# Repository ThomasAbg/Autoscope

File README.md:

# Autoscope

Autoscope is a 3D printed Dobson telescope automated by a Raspberry-Pi 3.

## Dependent repositories

The Yocto layer to build the telecope OS :

- https://github.com/thomaslepoix/meta-autoscope

The Stellarium plugin to control the telescope :

- https://github.com/thibaudledo/Autoscope-Stellarium-plugin

<br>

## Branch & release organization

- [branch : master](https://github.com/thibaudledo/Autoscope/tree/master) : Readme & main software
- [release : alpha](https://github.com/thibaudledo/Autoscope/releases) : Out of the box packages (Stellarium, OS)
- [branch : hardware](https://github.com/thibaudledo/Autoscope/tree/hardware) : 3D blender files & PCB kicad files
- [branch : doc](https://github.com/thibaudledo/Autoscope/tree/doc) : Documentation, datasheets, etc.
- [branch : latex](https://github.com/thibaudledo/Autoscope/tree/latex) : Latex documents
- [branch : hello_mod](https://github.com/thibaudledo/Autoscope/tree/hello_mod) : Exemple, helloworld kernel module
- [branch : mpu9250_mod](https://github.com/thibaudledo/Autoscope/tree/mpu9250_mod) : IMU driver
- [branch : a4988_mod](https://github.com/thibaudledo/Autoscope/tree/a4988_mod) : Motors & position sensors driver
- [branch : mtk3339d](https://github.com/thibaudledo/Autoscope/tree/mtk3339d) : GPS driver

<br>

## Download & work on this repository

```
mkdir Autoscope/
cd Autoscope/
git clone https://github.com/thibaudledo/Autoscope -b master Master
git clone https://github.com/thibaudledo/Autoscope -b doc Documentation
git clone https://github.com/thibaudledo/Autoscope -b latex Latex
git clone https://github.com/thibaudledo/Autoscope -b hardware Hardware

git clone https://github.com/thibaudledo/Autoscope -b hello_mod hello-mod
git clone https://github.com/thibaudledo/Autoscope -b mpu9250_mod mpu9250-mod
git clone https://github.com/thibaudledo/Autoscope -b a4988_mod a4988-mod
git clone https://github.com/thibaudledo/Autoscope -b mtk3339d mtk3339d
```

<br>

## Authors

- [Thibaud Le Doledec](https://github.com/thibaudledo) `<thibaudledo@gmail.com>`
- [Thomas Lepoix](https://github.com/thomaslepoix) `<thomas.lepoix@protonmail.ch>`
- [Thomas Abgrall](https://github.com/ThomasAbg) `<01thomas.abgrall@gmail.com>`
- [Clément Ailloud](https://github.com/clement-ailloud) `<clem.ailloud@gmail.com>`

<br>

## Inspired by

- https://blog.dagoma.fr/telescope-imprime-en-3d/

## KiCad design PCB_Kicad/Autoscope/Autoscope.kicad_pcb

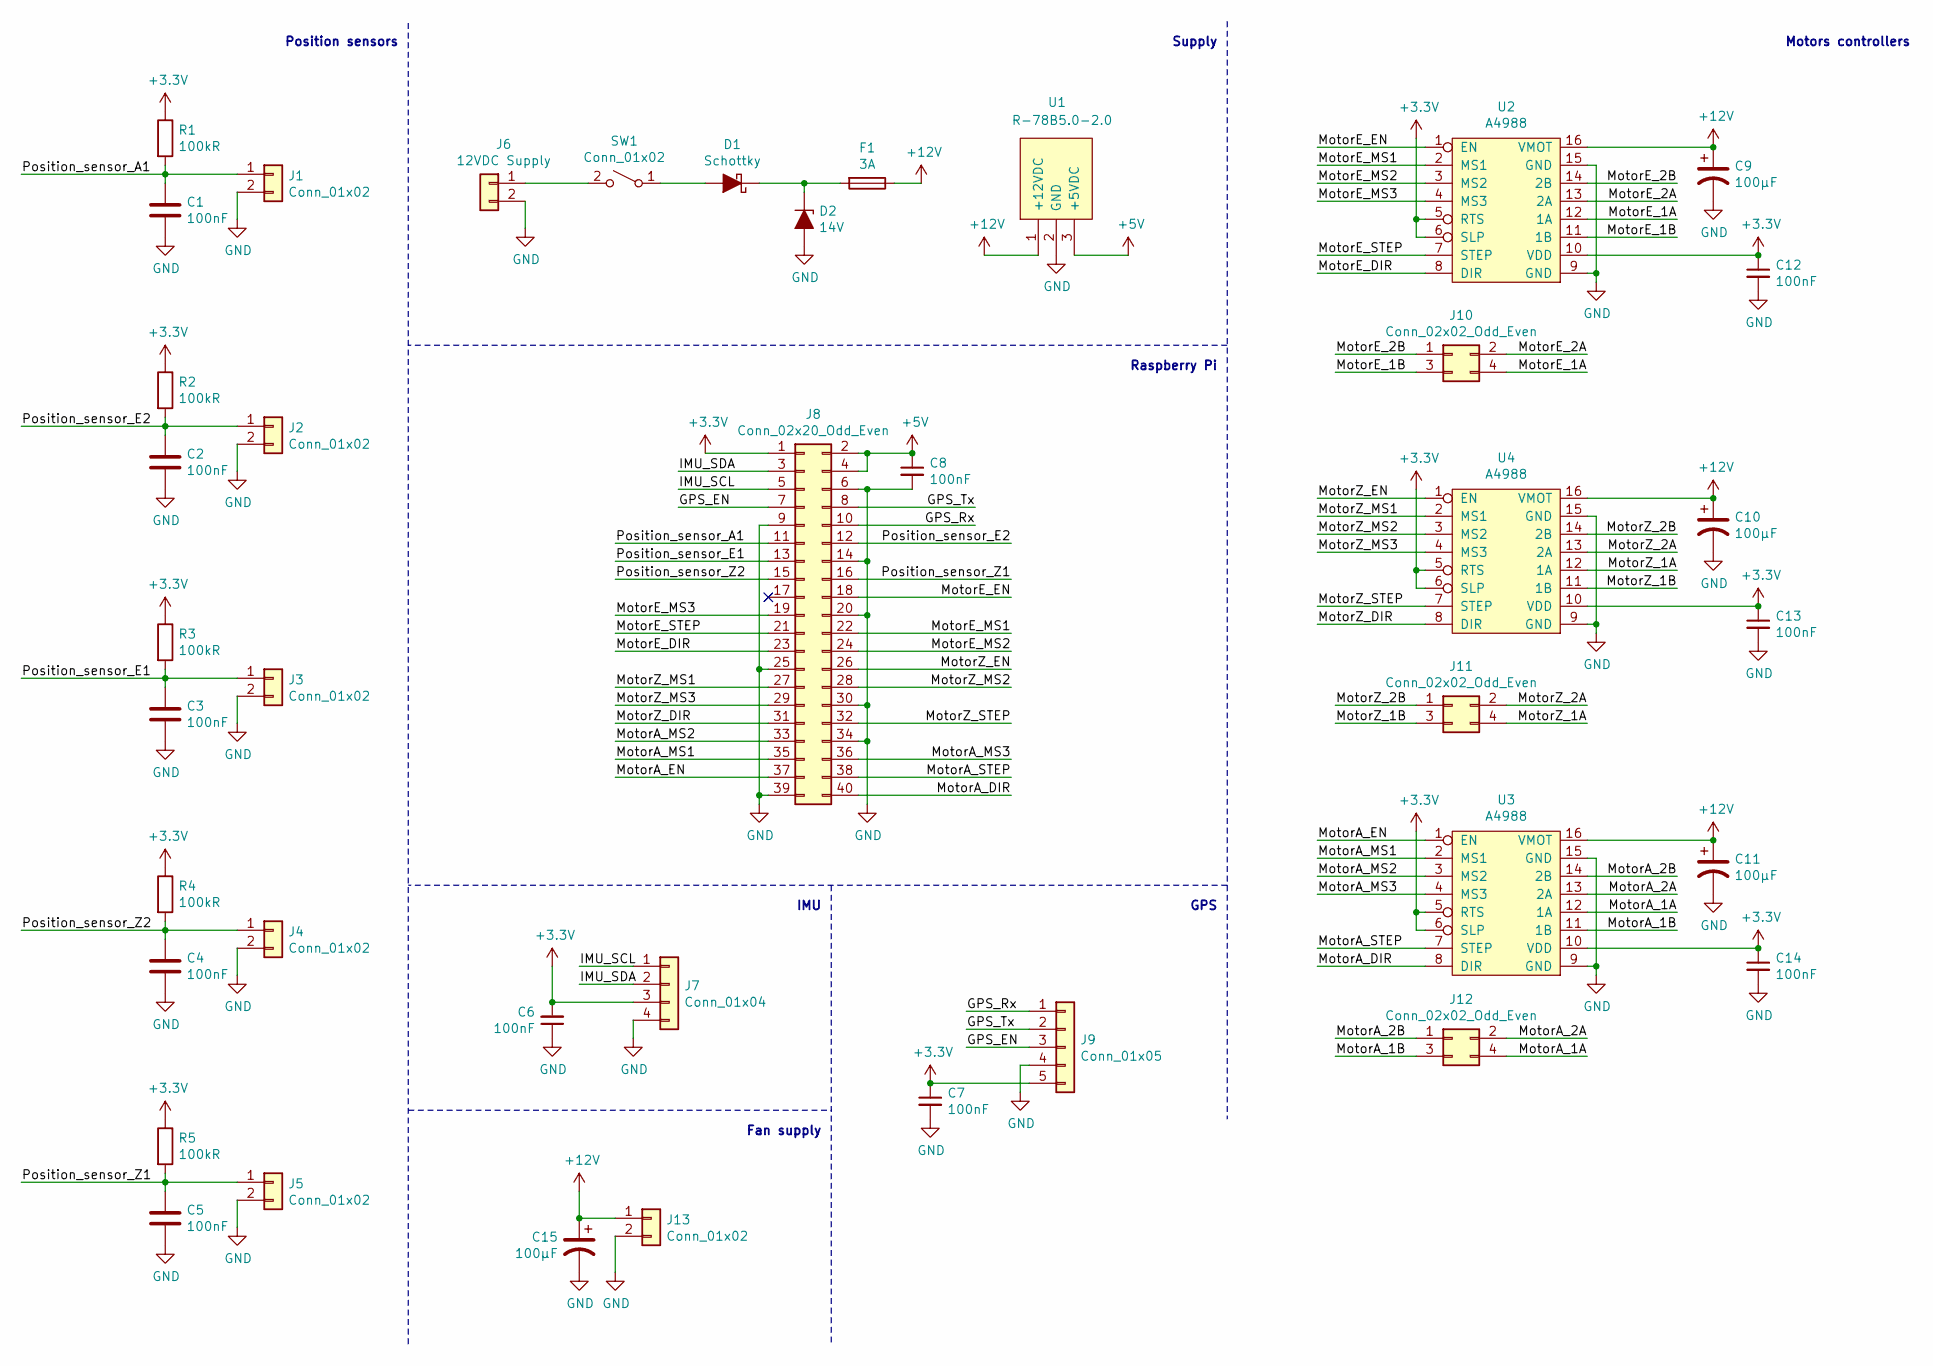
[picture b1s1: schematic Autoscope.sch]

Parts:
C1, C2, C3, C4, C5, C6, C7, C8, C12, C13, C14: 100nF; C_0805_2012Metric_Pad1.15x1.40mm_HandSolder
C9, C10, C11, C15: 100µF; CP_EIA-7343-43_Kemet-X_Pad2.25x2.55mm_HandSolder
D1: Schottky; D_SMC_Handsoldering
D2: 14V; D_SMC_Handsoldering
F1: 3A; Fuseholder5x20_horiz_SemiClosed_Casing10x25mm
J1, J2, J3, J4, J5, J13: Conn_01x02; PinHeader_1x02_P2.54mm_Horizontal
J6: 12VDC Supply; PJ-043H
J7: Conn_01x04; PinHeader_1x04_P2.54mm_Horizontal
J8: Conn_02x20_Odd_Even; PinSocket_2x20_P2.54mm_Vertical
J9: Conn_01x05; PinHeader_1x05_P2.54mm_Horizontal
J10, J11, J12: Conn_02x02_Odd_Even; PinHeader_2x02_P2.54mm_Horizontal
R1, R2, R3, R4, R5: 100kR; R_0805_2012Metric_Pad1.15x1.40mm_HandSolder
SW1: Conn_01x02; PinHeader_1x02_P2.54mm_Horizontal
U1: R-78B5.0-2.0; R-78B-2.0
U2, U3, U4: A4988

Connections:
+3V3: C6.2, C7.1, C12.1, C13.1, C14.1, J7.3, J8.1, J9.5, R1.1, R2.1, R3.1, R4.1, R5.1, U2.5 (RTS), U2.6 (SLP), U2.10 (VDD), U3.5 (RTS), U3.6 (SLP), U3.10 (VDD), U4.5 (RTS), U4.6 (SLP), U4.10 (VDD)
+5V: C8.1, J8.2, J8.4, U1.3 (+5VDC)
+12V: C9.1, C10.1, C11.1, C15.1, F1.1, J13.1, U1.1 (+12VDC), U2.16 (VMOT), U3.16 (VMOT), U4.16 (VMOT)
/GPS_EN: J8.7, J9.3
/GPS_Rx: J8.10, J9.1
/GPS_Tx: J8.8, J9.2
/IMU_SCL: J7.1, J8.5
/IMU_SDA: J7.2, J8.3
/MotorA_1A: J12.4, U3.12 (1A)
/MotorA_1B: J12.3, U3.11 (1B)
/MotorA_2A: J12.2, U3.13 (2A)
/MotorA_2B: J12.1, U3.14 (2B)
/MotorA_DIR: J8.40, U3.8 (DIR)
/MotorA_EN: J8.37, U3.1 (EN)
/MotorA_MS1: J8.35, U3.2 (MS1)
/MotorA_MS2: J8.33, U3.3 (MS2)
/MotorA_MS3: J8.36, U3.4 (MS3)
/MotorA_STEP: J8.38, U3.7 (STEP)
/MotorE_1A: J10.4, U2.12 (1A)
/MotorE_1B: J10.3, U2.11 (1B)
/MotorE_2A: J10.2, U2.13 (2A)
/MotorE_2B: J10.1, U2.14 (2B)
/MotorE_DIR: J8.23, U2.8 (DIR)
/MotorE_EN: J8.18, U2.1 (EN)
/MotorE_MS1: J8.22, U2.2 (MS1)
/MotorE_MS2: J8.24, U2.3 (MS2)
/MotorE_MS3: J8.19, U2.4 (MS3)
/MotorE_STEP: J8.21, U2.7 (STEP)
/MotorZ_1A: J11.4, U4.12 (1A)
/MotorZ_1B: J11.3, U4.11 (1B)
/MotorZ_2A: J11.2, U4.13 (2A)
/MotorZ_2B: J11.1, U4.14 (2B)
/MotorZ_DIR: J8.31, U4.8 (DIR)
/MotorZ_EN: J8.26, U4.1 (EN)
/MotorZ_MS1: J8.27, U4.2 (MS1)
/MotorZ_MS2: J8.28, U4.3 (MS2)
/MotorZ_MS3: J8.29, U4.4 (MS3)
/MotorZ_STEP: J8.32, U4.7 (STEP)
/Position_sensor_A1: C1.2, J1.1, J8.11, R1.2
/Position_sensor_E1: C3.2, J3.1, J8.13, R3.2
/Position_sensor_E2: C2.2, J2.1, J8.12, R2.2
/Position_sensor_Z1: C5.2, J5.1, J8.16, R5.2
/Position_sensor_Z2: C4.2, J4.1, J8.15, R4.2
GND: C1.1, C2.1, C3.1, C4.1, C5.1, C6.1, C7.2, C8.2, C9.2, C10.2, C11.2, C12.2, C13.2, C14.2, C15.2, D2.2 (A), J1.2, J2.2, J3.2, J4.2, J5.2, J6.2, J7.4, J8.6, J8.9, J8.14, J8.20, J8.25, J8.30, J8.34, J8.39, J9.4, J13.2, U1.2 (GND), U2.9 (GND), U2.15 (GND), U3.9 (GND), U3.15 (GND), U4.9 (GND), U4.15 (GND)
unnamed: D1.1 (K), D2.1 (K), F1.2
unnamed: D1.2 (A), SW1.1 (A)
unnamed: J6.1, SW1.2 (B)

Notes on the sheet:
GPS
IMU
Raspberry Pi
Supply
Motors controllers
Position sensors
Fan supply

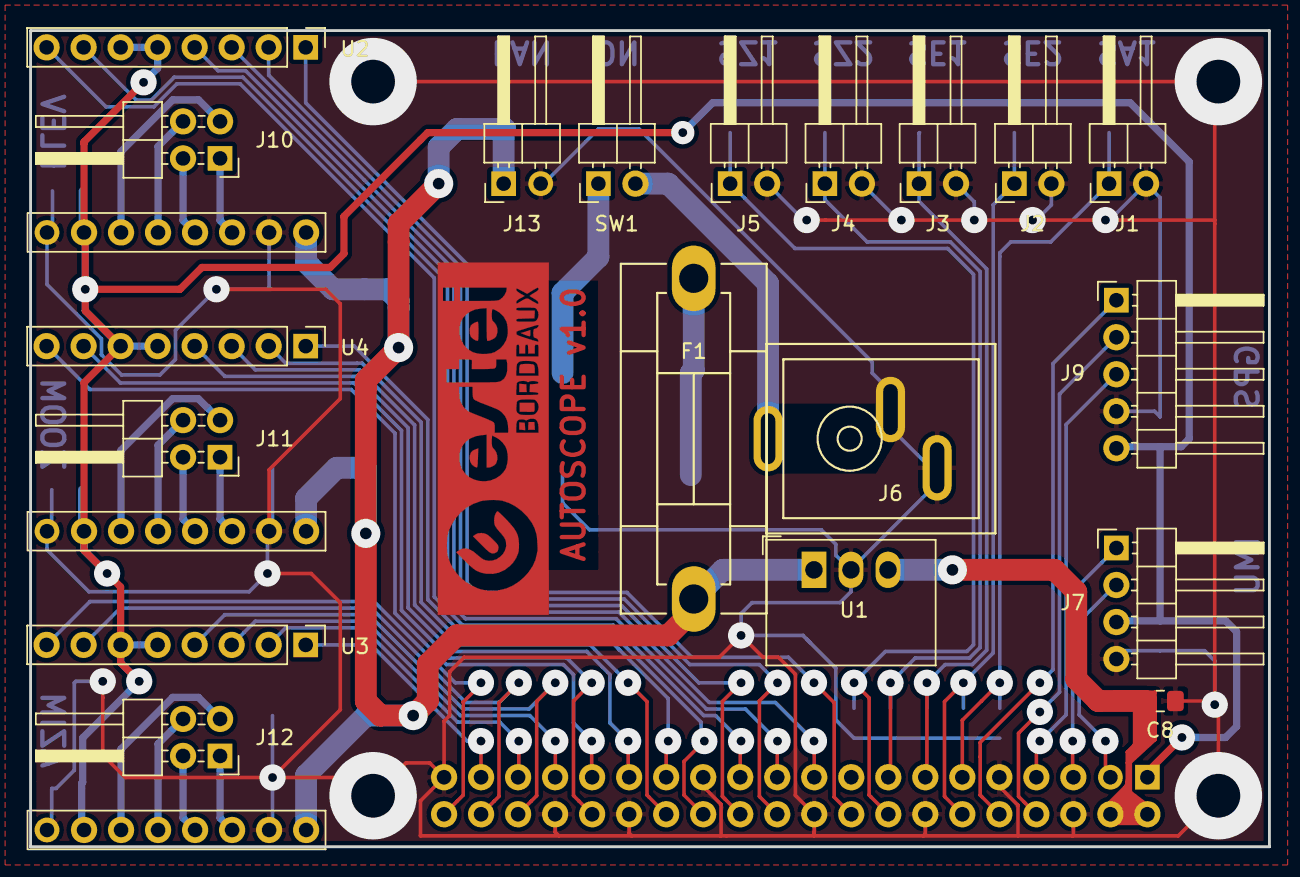
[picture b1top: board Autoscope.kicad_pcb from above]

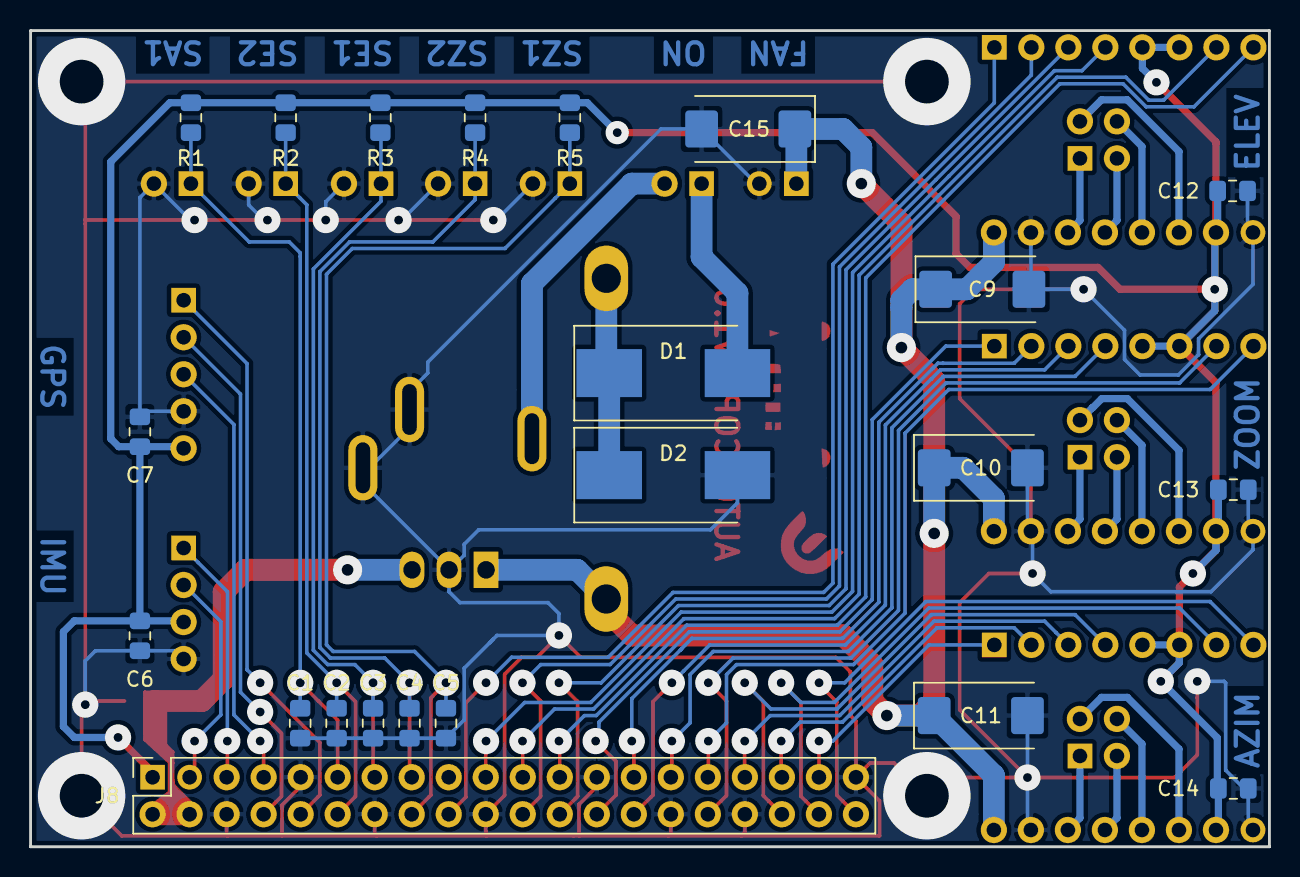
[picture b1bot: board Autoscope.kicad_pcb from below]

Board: 2 copper layers, 85.0 x 56.0 mm, 41 parts (22 on the bottom side), 47 nets.

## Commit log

2018-11-20 Adding documentation
2018-12-05 start Finite-state machine
2018-12-05 Branch reorganization
2018-12-05 README.md updated
2018-12-06 Template updated
2018-12-07 Add Compte_Rendu_1
2018-12-10 Compte rendu 1 updated
2018-12-26 add datasheets
2019-01-07 Controle writing pins
2019-01-07 add amsmath & estei.png to template
2019-01-07 move Figures
2019-01-08 mv compte rendu -> compte rendu 1
2019-01-08 add compte rendu 2
2019-01-08 Readme.md: update
2019-01-08 update part & add Lepoix
2019-01-08 Add mpu-9250 register map datasheet
2019-01-08 group part updated
2019-01-09 add part's thomas
2019-01-09 correction des fautes orthographe
2019-01-09 lepoix update
2019-01-09 puge build files
2019-01-09 add gitignore
2019-01-09 pdf updated
2019-01-09 add Autoscope_2.pdf
2019-01-21 add rpi & DC/DC datasheets
2019-01-21 mv mpu datasheet
2019-01-21 add sen-13762 & a4988 doc
2019-01-24 Add mpu9250 datasheet and register map
2019-01-24 Solved deleted file
2019-01-29 add sch
2019-01-29 rm picopi & add rpi pinout & add supply connector
2019-01-30 update sch & create pcb
2019-01-30 add headers doc
2019-02-06 schematic ok & pcb in progress
2019-02-07 add autoscope 3
2019-02-10 nearly finished pcb
2019-02-10 add BOM
2019-02-13 really nearly finished pcb & 3D models
2019-02-13 Add zoom, not tested
2019-02-18 Add Makefile
2019-02-19 initial commit hello_mod branch
2019-02-20 maj gestion_mot
2019-03-04 finalize PCB files
2019-03-06 CR 4é
2019-03-08 add compte rendu 4
2019-03-08 rm .odt
2019-03-08 ready to print PCB
2019-03-13 add A5 fab files
2019-03-13 Revert "add A5 fab files"
    This reverts commit e4fdc3836b1555d306f2fe8898c2b94182f1870a.
2019-03-13 add A4 fab files with logo
2019-03-26 add hello-mod probe messages
2019-03-26 180 flip motor controller 3D model
2019-04-01 180 flip controllers on main .png
2019-04-02 clean new independant branch
2019-04-04 add README
2019-04-04 add blender preview to README
2019-04-10 update BOM
2019-04-10 refactor labels & fix a bug : invert GPS_EN GPS_Rx
2019-04-10 3D models : 180 flip a4988
2019-04-10 README : add main components
2019-04-10 BOM : add fan & CSI cable
2019-04-10 BOM fix unconsidered lines
2019-04-13 mv a4988 to dedicated branch
2019-04-13 add license GPLV2
2019-04-14 add Compte Rendu 5
2019-04-14 README add links to branchs and releases
2019-04-14 add / remove & rename datasheets
2019-04-14 Compte Rendu 5 update
2019-04-14 README : add equations & lists
2019-04-14 Add chapter 3
2019-04-14 Compte Rendu 5 : add personnal tasks
2019-04-18 Create COPYING
2019-04-18 Makefile yocto compatible
2019-04-20 ADD CODE MAJ
2019-04-23 upload clement's mpu driver
2019-04-23 Makefile : try i2c & spi drivers
2019-04-23 WHOAMI reg addr 0x73 -> 0x75
2019-04-23 add Compte rendu 6 LEPOIX
2019-04-24 push code in good branch
2019-04-25 CR6 Lepoix update
2019-04-25 rm A4988
2019-04-27 README : add connection sch
2019-05-05 CR6 : update lepoix & begin CDC
2019-05-10 CR6 : add group chapters
2019-05-11 upload test fragments
2019-05-11 update gps driver link
2019-05-11 restore IPC test
2019-05-12 update parser fragment
2019-05-18 initised macros
2019-05-18 add operational daemon
2019-05-18 rm test fragments
2019-05-19 MAJ GPIO
2019-05-20 Change nb pin
2019-05-20 Correction my_init size tab
2019-05-20 Correctif ioctl
2019-05-20 change name device create
2019-05-20 .sh fix status) with busybox
2019-05-20 add regex url
2019-05-21 Add stopOne moteur zoom
2019-05-21 add gps daemon & motor driver test fragments
2019-05-27 add stellarium plugin tuto
2019-05-28 update Makefile -> clement's version
2019-05-28 CR6 update LEPOIX & group parts
2019-05-29 check MPU_9250_DEVICE_ID instead of MPU_9255_DEVICE_ID
2019-05-29 Add Part Abgrall
2019-05-29 Add Abgrall part
2019-05-29 refactor makefile
2019-05-29 move branch mpu_9250_mod -> mpu9250_mod
2019-05-29 update LEPOIX & GROUP
2019-05-29 Edit Part Abgrall
2019-05-29 update all et ABGRALL refactor
2019-05-29 CR6 final update?
2019-05-29 add Autoscope_6.pdf
2019-05-29 add Collimation.pdf
2019-05-29 add persistent mode & fix missing 3rd group in altitude regex
2019-05-30 add github links to signatures
2019-06-01 Dev ioctl
2019-06-03 add IOCTL
2019-06-03 Correction value variable
2019-06-03 Correction driver
2019-06-03 Correction driver copy_from_user rotation
2019-06-03 Correction driver switch case ROTATION
2019-06-03 Correction driver copy_from_user
2019-06-03 retrun old version for test
2019-06-04 rename
2019-06-04 rename header
2019-06-04 Old version sans define ioctl
2019-06-04 modif define ioctl clr heaader
2019-06-04 init tableauoutput lenght
2019-06-04 gpio free
2019-06-04 Correctif tableauoutput busy with New version
2019-06-04 Correction define status
2019-06-04 lenght Data ioctl
2019-06-05 add CR6 Oral
2019-06-05 update CR6 Oral group & LEPOIX
2019-06-06 copy-user
2019-06-10 modif ioctl
2019-07-17 Try passing struct in ioclt
2019-07-29 lepoix : gmail -> protonmail
